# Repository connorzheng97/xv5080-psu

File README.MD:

# DIY Power Supply for Roland XV-5080

This is a replacement power supply for the Roland XV-5080. It uses 3 commercial off-the-shelf MEANWELL power supplies and a custom PCB with LDO to condition the power rails.

## LDO Board

The LDO board sits between the 3 SMPS and the rest of the synthesizer to clean the power rails. The board is designed using KiCAD 10. Digital and analog gound are separate to avoid gound loop. Assemble the board as indicated, in case KiCAD is not used, production files are provided. A interactive BOM is provided for manual soldering. 

I used 7.62mm screw type terminal block to connect the DC input but you can also just solder wires directly to the board. 

The 5V LDO is MIC29502, which can be replaced with MIC29302 if it's difficult to source. The +15V LDO is LT1963 which can be replaced with TL1963. The -15V LDO is LT3015.

## PSU Chassis

The 3 SMPS and the LDO board are all mounted on the chassis and is mounted into the XV-5080 as one assembly. The chassis will be mounted using the 4 holes for the factory power supply.

The chassis is 3D-printed. Recommended printing parameters are: no support, 0.2mm or lower layer height, 100% infill, using ABS or ASA. PLA or PETG are not recommended as those can degrade or deform if the synthesizer is subjected to high heat (for example during transportation in a vehicle).

After printing is finished, 4 M3 nuts need to be pressed into the hexagonal receiving slot. These embedded nuts will hold the entire PSU to the XV-5080.

## PSU Assembly

**Please make sure you are qulified to work with mains electrical. Risk of electric shock. Must use grounded AC mains connection.**

### Components

To make a complete set of power supply you'll need the following components:

- 1x mounting chassis (3D printed, STL is provided)
- 2x MEANWELL RS-15-15
- 1x MEANWELL RS-25-5
- 1x LDO board (design file and manufacturing file provided)
- 4x M3 nut (for embedding into chassis)
- 10x M3x8 countersink screw (for mounting SMPS and board to PSU chassis)
- 4x M3x15 standoff/spacers, female-female (for LDO board)
- 8x M3x8 pan head screw (for LDO board mounting and PSU chassis to XV-5080 mounting)
- 18AWG or larger gauge wire rated for >=300V like 1007 or 1569
- 1x 3.2mm ring crimp terminal and crimping tool (for PE)
- 21x 3.2mm fork type crimp terminal and crimping tool (optional)
- VH3.96 connector set and crimping tool (optional, can re-use original wire harness)
- 1x AC connector IEC C14 SCHURTER 6100.4312 (optional, if replacing original AC connector)

The 3 switch mode power supply can be subsituted with other model but you must make sure their outputs are isolated from the PE and chassis.

### Assembly Steps
1. Mount the 3 SMPS to the chassis using 6 M3 countersink screws

2. Mount the LDO board to the chassis using 4 M3 countersink screws, 4 spacers and 4 pan head screws

3. Make the AC side electrical connection using wire (18AWG or larger), optionally with fork type crimp terminals. The power switch is wired inline in L line between the AC input and the SMPSs, the factory connector for the switch is VH3.96. Wire all 3 SMPS AC inputs together.

   - AC INPUT PE ---- XV-5080 chassis and 3 SMPS PE
   - AC INPUT L ---- Switch ---- 3 SMPS L
   - AC INPUT N ---- 3 SMPS N

4. Make DC side electrical connection using wire (18AWG or larger), optionally with fork type crimp terminals. 

   - RS-25-5 +V ---- LDO Board +5.5VIN
   - RS-25-5 -V ---- LDO Board DGND
   - first RS-15-15 +V ---- LDO Board +16VIN
   - first RS-15-15 -V ---- LDO Board AGND
   - second RS-15-15 +V ---- LDO Board AGND
   - second RS-15-15 -V ---- LDO Board -16VIN

5. Remove original power supply standoff. Put assembly into synthesizer, connect or solder switch and AC input. Wire PE connection to the chassis using a ring crimp terminal. Do not mount the PSU to synthesizer or connect output yet. See image for recommended grounding location

6. Connect AC power and turn on power. Using a multimeter to measure the output of the SMPS. Adjust 5V SMPS output to 5.7V, 15V SMPS output to 16.5V. Verify LDO board output voltage using multimeter.
7. Remove AC power and disconnect AC input cable, connect LDO board output to synthesizer using original cable.
8. Mount PSU chassis to XV-5080 using 4 M3x8 pan head screws
9. Apply power again and test functionality.

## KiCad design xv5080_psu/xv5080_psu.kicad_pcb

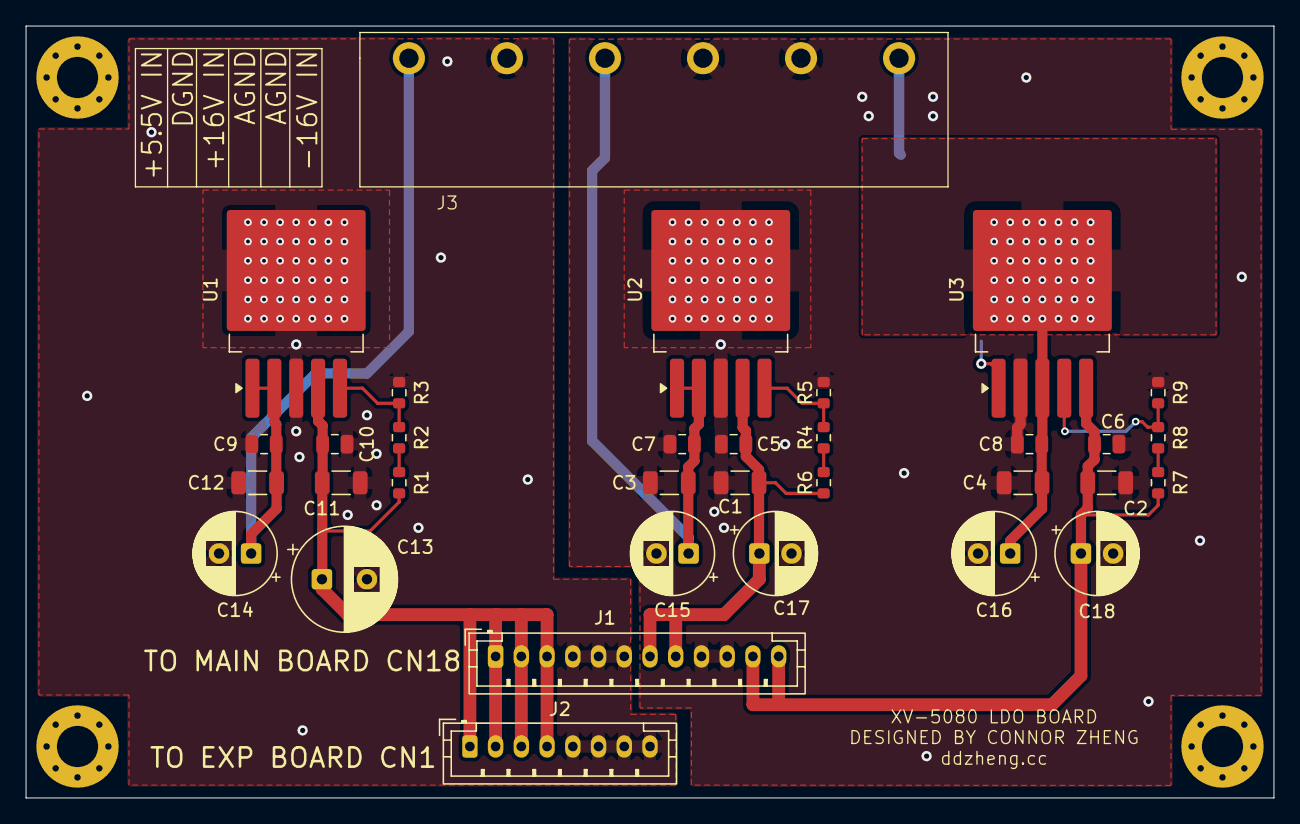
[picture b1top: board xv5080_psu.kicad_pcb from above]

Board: 2 copper layers, 97.0 x 60.0 mm, 37 parts (0 on the bottom side), 14 nets.

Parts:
C1, C2, C3, C4: 25V/22uF/X5R; C_1206_3216Metric
C5, C6, C7, C8, C9, C10: 100nF; C_0805_2012Metric
C11, C12: 10V/47uF/X5R; C_1206_3216Metric
C13: 10V/470uF; CP_Radial_D8.0mm_P3.50mm
C14: 10V/220uF; CP_Radial_D6.3mm_P2.50mm
C15, C16, C17, C18: 25V/220uF; CP_Radial_D6.3mm_P2.50mm
H1, H2, H3, H4: MountingHole; MountingHole_3.2mm_M3_Pad_Via
J1: JST_PH_B12B-PH-K; JST_PH_B12B-PH-K_1x12_P2.00mm_Vertical
J2: JST_PH_B8B-PH-K; JST_PH_B8B-PH-K_1x08_P2.00mm_Vertical
J3: ScrewTerminal_7.62_4p; CONN_ScrewTerminal_KF-7.62-6P
R1: 360R; R_0603_1608Metric
R2: 3.6R; R_0603_1608Metric
R3: 120R; R_0603_1608Metric
R4: 13K; R_0603_1608Metric
R5: 1.3K; R_0603_1608Metric
R6: 1.8K; R_0603_1608Metric
R7: 0R; R_0603_1608Metric
R8: 140K; R_0603_1608Metric
R9: 12.4K; R_0603_1608Metric
U1: MIC29502WU; TO-263-5_TabPin3
U2: LT1963EQ; TO-263-5_TabPin3
U3: LT3015Q; TO-263-5_TabPin3

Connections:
+5V: C10.1, C11.1, C13.1, J1.1, J1.2, J1.3, J2.1, J2.2, J2.3, J2.4, R1.1, U1.4 (VOUT)
+15V: C1.1, C5.1, C17.1, J1.7, J1.8, R6.1, U2.4 (OUT)
-15V: C2.1, C6.1, C18.1, J1.11, J1.12, R7.1, U3.5 (OUT)
/+5VIN: C9.1, C12.1, C14.1, J3.1, U1.1 (EN), U1.2 (VIN)
/+15VIN: C3.1, C7.1, C15.1, J3.3, U2.1 (~SHDN), U2.2 (IN)
/-15VIN: C4.1, C8.1, C16.1, J3.6, U3.1 (~SHDN), U3.3 (IN)
GND: C9.2, C10.2, C11.2, C12.2, C13.2, C14.2, J1.4, J1.5, J1.6, J2.5, J2.6, J2.7, J2.8, J3.2, R3.2, U1.3 (GND)
GNDA: C1.2, C2.2, C3.2, C4.2, C5.2, C6.2, C7.2, C8.2, C15.2, C16.2, C17.2, C18.2, J1.9, J1.10, J3.4, J3.5, R5.2, R9.2, U2.3 (GND), U3.2 (GND)
unnamed: R1.2, R2.1
unnamed: R4.1, R6.2
unnamed: R7.2, R8.1
unnamed: R2.2, R3.1, U1.5 (ADJ)
unnamed: R4.2, R5.1, U2.5 (ADJ)
unnamed: R8.2, R9.1, U3.4 (ADJ)

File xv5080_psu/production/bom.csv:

Designator,Footprint,Quantity,Value,LCSC Part #
"C1, C2, C3, C4",1206,4,25V/22uF/X5R,
"C10, C5, C6, C7, C8, C9",0805,6,100nF,
"C11, C12",1206,2,10V/47uF/X5R,
C13,CP_Radial_D8.0mm_P3.50mm,1,10V/470uF,
C14,CP_Radial_D6.3mm_P2.50mm,1,10V/220uF,
"C15, C16, C17, C18",CP_Radial_D6.3mm_P2.50mm,4,25V/220uF,
J1,JST_PH_B12B-PH-K_1x12_P2.00mm_Vertical,1,JST_PH_B12B-PH-K,
J2,JST_PH_B8B-PH-K_1x08_P2.00mm_Vertical,1,JST_PH_B8B-PH-K,
J3,CONN_ScrewTerminal_KF-7.62-6P,1,ScrewTerminal_7.62_4p,
R1,0603,1,360R,
R2,0603,1,3.6R,
R3,0603,1,120R,
R4,0603,1,13K,
R5,0603,1,1.3K,
R6,0603,1,1.8K,
R7,0603,1,5.6K,
R8,0603,1,130K,
R9,0603,1,12K,
U1,TO-263-5_TabPin3,1,MIC29502WU,
U2,TO-263-5_TabPin3,1,LT1963EQ,
U3,TO-263-5_TabPin3,1,LT3015Q,
